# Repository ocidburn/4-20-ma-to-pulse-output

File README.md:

# AM24 — преобразователь 4–20 мА → частота / импульсы

Прототип на NUCLEO-G474RE с изолированным входом на AD7124-4. ТЗ, расчёт погрешностей, описание схемы, перечень элементов с ценами и методика калибровки — в [docs/AM24_spec.pdf](docs/AM24_spec.pdf).

```
docs/       ТЗ и описание схемы (PDF)
firmware/   прошивка STM32G474 (CMake, без HAL, регистры CMSIS)
hardware/   схема и печатная плата шилда (KiCad 10), PDF, перечень элементов, файлы для заказа (fab/)
tools/      утилита на ПК (am24.py), генераторы схемы и печатной платы KiCad (Python)
```

Заголовки CMSIS подключены как подмодули git, поэтому клонируйте с ними:

```bash
git clone --recursive https://github.com/ocidburn/4-20-ma-to-pulse-output.git
```

Если репозиторий уже склонирован без них: `git submodule update --init`. На Windows перед этим может понадобиться `git config --global core.longpaths true`.

## Прошивка

### Сборка

Нужны CMake (есть в `C:\Program Files (x86)\CMake`) и компилятор из STM32CubeIDE 2.1.1 — его путь находится автоматически, другой можно указать через `-DARM_TOOLCHAIN_DIR=<папка bin>`. Ninja тоже берётся из CubeIDE.

```bash
cd firmware
cmake -S . -B build -G Ninja
cmake --build build
```

Результат: `build/am24.elf`, `am24.hex`, `am24.bin` (≈ 35 КБ flash, 10 КБ RAM).
Без TCXO (на внутреннем генераторе, только для отладки): `cmake -S . -B build -G Ninja -DUSE_HSI=ON`.

### Прошивка платы

Проще всего скопировать `build/am24.bin` на диск NOD_G474RE, который Nucleo создаёт при подключении по USB. Либо открыть `am24.elf` в STM32CubeProgrammer.

### Выводы (Arduino-разъём Nucleo)

| Вывод | Arduino | Назначение |
|---|---|---|
| PA5 / PA6 / PA7 | D13 / D12 / D11 | SPI1 SCK / MISO / MOSI → ISO7741 → AD7124 |
| PB6 | D10 | CS AD7124 |
| PA0 | A0 | частотный выход (TIM5_CH1) |
| PA1 | A1 | импульсный выход |
| PA4 | A2 | светодиод «Авария» |
| PA2 / PA3 | — | LPUART1 → виртуальный COM-порт ST-LINK, 115200 8N1 |
| PF0 | — | вход 10 МГц от TCXO (HSE bypass) |
| PB10 | D6 | PPS от модуля GPS (TIM2_CH3), разъём J7 на шилде |

**Перед запуском с TCXO** проверьте по руководству Nucleo-G474RE (UM2505), какие перемычки (solder bridges) перепаять, чтобы подать внешний такт на OSC_IN. Если HSE не запустится, прошивка сама перейдёт на внутренний генератор и сообщит об этом при старте («HSI (inaccurate!)»).

### Как работает

- АЦП: секвенсор перебирает три канала, ≈ 150 мс на круг. Каналы 0 и 1 — шунт в прямом (AIN0−AIN1) и обратном (AIN1−AIN0) порядке: полуразность пары убирает смещение АЦП и его дрейф. Канал 2 — AIN6, делитель термистора NTC от опоры. Биполярный режим, усиление 1, буферы включены (у канала NTC без буфера AIN−), опора REFIN1 = 3,0 В, пост-фильтр 20 отсч./с (подавление 50/60 Гц).
- Температурная поправка: ток × (1 − `tc_ppm`·10⁻⁶·(T − T₀)), где T — температура по NTC, T₀ — запоминается командой `CAL CLEAR`. Затем калибровка — кусочно-линейная, до 11 точек.
- Частота: 32-битный TIM5 на 170 МГц, период в формате 32.32 с дробным накоплением — средняя частота точна до долей ppm, отдельный период отличается не больше чем на 1 такт (5,9 нс).
- Импульсы: каждые 1 мс расход интегрируется от того же генератора; целые импульсы копятся в счётчике и выдаются с заданной длительностью (пауза = длительности). Поправка генератора действует и на импульсы.
- GPS: TIM2 захватывает фронты PPS; ошибка TCXO считается за окно `gps_win` секунд (по умолчанию 100, разрешение ≈ 0,001 ppm) и сразу применяется. Без PPS работает последняя измеренная поправка, после перезапуска — `tcxo_ppm`. На каждом фронте PPS запоминается точная сумма импульсов с дробной частью — по ней утилита проверяет импульсный выход.
- Аварии: ток < `alarm_lo` или > `alarm_hi` (NE43), ошибка АЦП или нет данных 500 мс, переполнение буфера импульсов. Бит 0x10 — термистор не отвечает или температура ушла от калибровочной больше чем на `t_window`: только светодиод, выходы работают.
- Настройки и калибровка хранятся в последней странице flash. **Во время SAVE выходы замирают примерно на 25 мс.**

### Команды (терминал 115200 8N1, каждая строка заканчивается `OK` или `ERR ...`)

| Команда | Что делает |
|---|---|
| `*IDN?` | идентификация |
| `MEAS?` | ток, частота, расход, сумматор, температура, поправка генератора, аварии |
| `RAW?` | ток до калибровки (с поправкой и без), его среднее за 3 с, температура |
| `WIN START` / `WIN?` | окно усреднения: среднее всех пар с момента `WIN START` |
| `CONF?` | все настройки |
| `SET <ключ> <значение>` | изменить настройку (действует сразу, `SAVE` — сохранить) |
| `CAL?` / `CAL CLEAR` / `CAL ADD <мА>` | точки калибровки (до 11); `CAL ADD` берёт среднее окна, если оно открыто |
| `SAVE` / `DEFAULTS` | сохранить / заводские настройки |
| `TOTAL?` / `TOTAL RESET` | сумматор импульсов (`EXACT` — с дробной частью) |
| `GPS?` / `GPS STORE` | состояние PPS и измеренная ошибка генератора / записать её в `tcxo_ppm` (затем `SAVE`) |
| `FTEST <Гц>` / `FTEST OFF` | принудительная частота для калибровки генератора |

Ключи настроек: `fmin`, `fmax` (Гц), `cutoff` (% диапазона), `damp` (с), `qmax` (ед./ч при 20 мА), `pval` (ед./имп), `pwidth` (мс), `ppol` (1 — активный высокий уровень на PA1), `alarm_mode` (0 — 0 Гц, 1 — `alarm_freq`, 2 — удержание), `alarm_freq`, `alarm_lo`, `alarm_hi` (мА), `tcxo_ppm`, `gps` (1 — поправка по GPS), `gps_win` (с), `vref`, `rshunt`, `tc_ppm` (ppm/°C), `t_window` (°C), `ntc_r25`, `ntc_beta`, `ntc_rfix`.

Настройки версии 0.2 несовместимы с 0.1: после прошивки действуют заводские, калибровку нужно выполнить заново.

## Утилита на ПК

```bash
pip install pyserial pyvisa pyvisa-py
python tools/am24.py ports                      # список COM-портов
python tools/am24.py -p COM5 meas --watch       # показания
python tools/am24.py -p COM5 set qmax 50 --save
python tools/am24.py -p COM5 gps                # PPS и ошибка генератора; --store — сохранить её
python tools/am24.py -p COM5 --rref 100.000123 --dmm GPIB0::22::INSTR --dmm-type hp3458 tempco --apply
python tools/am24.py -p COM5 --rref 100.000123 --dmm GPIB0::22::INSTR --dmm-type hp3458 cal
python tools/am24.py -p COM5 --rref 100.000123 --dmm GPIB0::22::INSTR --dmm-type hp3458 verify
python tools/am24.py -p COM5 --rref 100.000123 --dmm GPIB0::22::INSTR --dmm-type hp3458 pulses --seconds 1000
python tools/am24.py -p COM5 log --interval 1   # журнал в CSV
python tools/am24.py --sim cal                  # пробный прогон без железа
```

- `--rref` — сопротивление эталонного резистора из сертификата; `--rref-tc` и `--rref-temp` пересчитывают его на текущую температуру.
- `--dmm` — адрес мультиметра в VISA (GPIB, USB, LAN или COM). `--dmm-type scpi` (по умолчанию) — Keysight, Fluke, Keithley; `hp3458` — язык 3458A. `--dmm-init` задаёт свои команды настройки. Без `--dmm` среднее за окно вводится вручную (запустите статистику на мультиметре, когда утилита попросит).
- `cal` — 9 точек от 4 до 20 мА, выдержка 20 с, окно 60 с (`--points`, `--settle`, `--window`). Утилита усредняет преобразователь (`WIN`) и мультиметр за одно и то же окно и показывает отклонение точек от гладкой кривой — так видна плохая точка.
- `verify` — 10 точек между точками калибровки, допуск `--limit-ppm` (по умолчанию 10 ppm диапазона = 0,001 %), отчёт CSV.
- `tempco` — температурный коэффициент `tc_ppm`: окна по 60 с в течение `--minutes` (по умолчанию 120) при 20 мА, пока температура под крышкой меняется хотя бы на 0,5 °C. Выполнять до калибровки.
- `pulses` — проверка импульсного выхода по времени GPS: дробная сумма импульсов на фронтах PPS против тока эталона за то же число секунд.
- В неопределённость результата `verify` и `pulses` не входит погрешность самого эталона — её считают отдельно (см. документ, раздел «Калибровка и проверка»).

## Плата-шилд (KiCad)

`hardware/am24_shield.kicad_sch` — полная схема на листе A2 (93 элемента), формируется скриптом:

```bash
python tools/gen_wired.py
```

Элементы нарисованы стандартными символами KiCad и соединены проводниками. Шины питания (+24V, +5V, +3V3, +5V_ISO, +3V3_ISO, GND, AGND) показаны символами питания, метки остались только у сигналов FOUT, POUT, ALARM между выходными каскадами и разъёмом Nucleo и у NTC (делитель термистора к AIN6). ERC KiCad 10: 0 ошибок. Рядом лежат `am24_shield.pdf`, нетлист и `am24_shield_bom.csv` — перечень элементов.

Клеммы выходов X3/X4: **1 — OC, 2 — PP (24 В), 3 — 0 В**.

Для режима 0,001 % добавлены термистор RK1 с делителем R9, C33 (ставится вплотную к DA1 и R2, всё под одной крышкой) и разъём J7 для модуля GPS: 1 +5V, 2 +3V3, 3 GND, 4 PPS → R10 → D6.

Старый вариант схемы на метках (`tools/gen_schematic.py`) перезаписывает тот же файл — не запускайте его. Совпадение соединений двух вариантов проверяется так (`am24_shield_labels.net` — нетлист старого варианта):

```bash
cd hardware
python ../tools/cmp_net.py am24_shield_labels.net am24_shield.net
```

- Цоколёвки AD7124-4, ISO7741, LTC6655, ADP7118, NXE1, ASTX-H11 и R-78HB сверены с документацией производителей.
- Стандартные цоколёвки DN2540N5 (G-D-S), NTD3055L104 (G-D-S), BCP56/BCP53 (B-C-E) и BAV199 (1 — анод D1, 2 — катод D2, 3 — общий) из текста документации не подтверждены — сверить с чертежами.
- F1 и F2 (Bourns MF-R005-0 и MF-R050) используют посадочное место `AM24:Fuse_Bourns_MF-R_8.0x3.1mm_P5.10mm` из библиотеки проекта `hardware/am24.pretty` (подключена через `hardware/fp-lib-table`). Сделано по размерам из документации Bourns: шаг 5,1 мм, выводы с двух сторон диска ≈ 1,8 мм друг от друга, отверстия 0,8 мм под выводы 0,405–0,51 мм. Модели SamacSys сюда не кладутся: их лицензия запрещает распространять их в виде библиотеки, а репозиторий публичный. У ADP7118 сверить размер теплового пятна с документацией.
- Добавлены 10 кОм на выводы МК (выходные каскады выключены при сбросе) и балласт R6 270 Ом для NXE1 (модулю нужно не меньше 10 % нагрузки).
- ERC: 0 ошибок, 48 предупреждений. 40 — символы, нарисованные генератором (MOSFET с перенумерованными выводами, прямоугольники микросхем, свои шины питания): они хранятся в самой схеме, отдельной библиотеки `am24` нет. 8 — BC847/BC857: в библиотеке KiCad они заданы через `extends`, а в схеме лежат развёрнутыми.

## Печатная плата

Два варианта одной платы 100 × 90 мм, ставится на разъёмы Arduino поверх NUCLEO-G474RE:

| Файл | Слои | Для чего |
|---|---|---|
| `hardware/am24_shield.kicad_pcb` | 4: сигналы / In1 — сплошные AGND и GND / In2 — сигналы и земля / сигналы и земля | основной: сплошная земля под аналоговой частью |
| `hardware/am24_shield_2layer.kicad_pcb` | 2: сигналы и заливка землёй с двух сторон | дешевле |

Файлы для заказа (Gerber, сверловка, координаты элементов) — `hardware/fab/*_fab.zip`, загружаются на JLCPCB или PCBWay как есть. Правила под их возможности: дорожка от 0,15 мм (обычно 0,2–0,3), зазор 0,2 мм, переходное 0,6/0,3 мм.

Как устроена плата:

- **Совмещение с Nucleo.** Разъёмы XS1–XS4 стоят в точках Arduino Uno R3 и ставятся снизу платы, штырями вниз в гнёзда Nucleo. Положение гнёзд и разъёмов Morpho на Nucleo-64 взято из стандарта Arduino и открытых посадочных мест Nucleo-64; **перед заказом распечатайте плату 1:1 и приложите к Nucleo**.
- **Выводные элементы только за пределами Nucleo.** Над Nucleo — только SMD, чтобы выводы не упирались в её детали и в штыри Morpho. Клеммники, TO-220, R-78, предохранители и J7 стоят на выступающей части платы.
- **Перемычки к Morpho.** CN7 оказывается под платой, поэтому над его выводами 29 (PF0, такт TCXO) и 6 (E5V, питание 5 В) прорезаны окна. J6 и J5 — SMD-штыри рядом с окнами; провод с гнёздами проходит через окно к выводу Morpho.
- **Изоляция.** Изолированная часть (вход, шунт, АЦП, ИОН, изолированное питание) — левый нижний угол. Барьер — полоса 4 мм без меди на всех слоях; через него переходят только ISO7741 (DD2) и NXE1 (U1). Земли: AGND на изолированной стороне, GND на остальной.
- **Шунт.** Измерительные линии S+ и S− проложены вручную прямо от площадок R2 к R3 и R4. Ток петли входит в R2.1 и выходит из R2.2 отдельными дорожками.
- **Крышка и радиатор.** Аналоговое ядро обведено на шелкографии («COVER») — сюда ставится крышка. Слева от VT1 место под небольшой радиатор TO-220 (на слое Fab).
- **OC-выходы.** Под DPAK VT21/VT22 — медные полигоны стока на трёх слоях (на 4-слойной) со сквозными переходными: тепло при КЗ на выходе.

Плата формируется скриптами (KiCad 10, Python KiCad и [Freerouting](https://github.com/freerouting/freerouting) 2.5, нужна Java 21+):

```bash
"C:\Program Files\KiCad\10.0\bin\python.exe" tools/gen_pcb.py --layers 4      # расстановка, барьер, правила, ручные дорожки
"C:\Program Files\KiCad\10.0\bin\python.exe" tools/route_pcb.py hardware/am24_shield.kicad_pcb --jar freerouting-2.5.0.jar
python tools/export_fab.py                                                      # архивы для заказа
```

`gen_pcb.py` перезаписывает плату: ручные правки в KiCad при этом теряются. Автотрассировщик каждый раз раскладывает дорожки немного по-разному.

DRC KiCad 10 для обоих вариантов: нет неразведённых цепей, нарушений зазоров и замыканий. Остаются предупреждения шелкографии (надписи частично налезают друг на друга и на площадки — завод срезает шелкографию с площадок сам) и одно о тепловом соединении площадки с заливкой. Превью: `hardware/am24_shield_top.png`, `am24_shield_bottom.png`, `am24_shield_2layer_top.png`; сборочный чертёж верхней стороны — `am24_shield_assembly_top.pdf`.

## Что не проверено

- Прошивка собрана, но на реальной плате не запускалась: нет железа. Обработка пар, температурная поправка, окна и GPS проверены только на симуляторе утилиты (`--sim`), он повторяет протокол, но не код прошивки.
- Команды мультиметров в `am24.py` (SCPI и язык 3458A) на приборах не проверялись.
- Адреса регистров AD7124, битовые поля и коды (пост-фильтр 20 отсч./с = FILTER 7 / POST_FILTER 5, режим full power = 2, ID 0x04/0x06/0x07) сверены с официальным драйвером ADI [no-OS ad7124.h / ad7124.c](https://github.com/analogdevicesinc/no-OS/tree/main/drivers/adc/ad7124). Электрические пределы (диапазон входов с буферами AVSS + 0,1 … AVDD − 0,1 В, опора 3,0 В при AVDD 3,3 В) сверены с документацией AD7124-4, ред. E.
- CRC на SPI АЦП не включён; связь контролируется флагом ошибки и тайм-аутом данных.
- Время установления АЦП при переключении трёх каналов взято равным периоду пост-фильтра (50 мс); на плате проверить по флагам и частоте пар.
- Плата не изготавливалась. Положение разъёмов Nucleo-64 и Morpho взято из стандарта Arduino и открытых посадочных мест, а не из чертежа ST: перед заказом сверить распечаткой 1:1.
- Медь стока под DPAK VT21/VT22 — около 0,7 см² на слой (≈ 2,2 см² на 4-слойной, ≈ 1,5 см² на 2-слойной), меньше 6 см² из расчёта. При длительном КЗ выхода OC на 30 В транзистор сильно греется; если такой режим возможен, снизить порог ограничения тока или увеличить полигон.
- Радиатор VT1 не выбран: на плате только место под него.

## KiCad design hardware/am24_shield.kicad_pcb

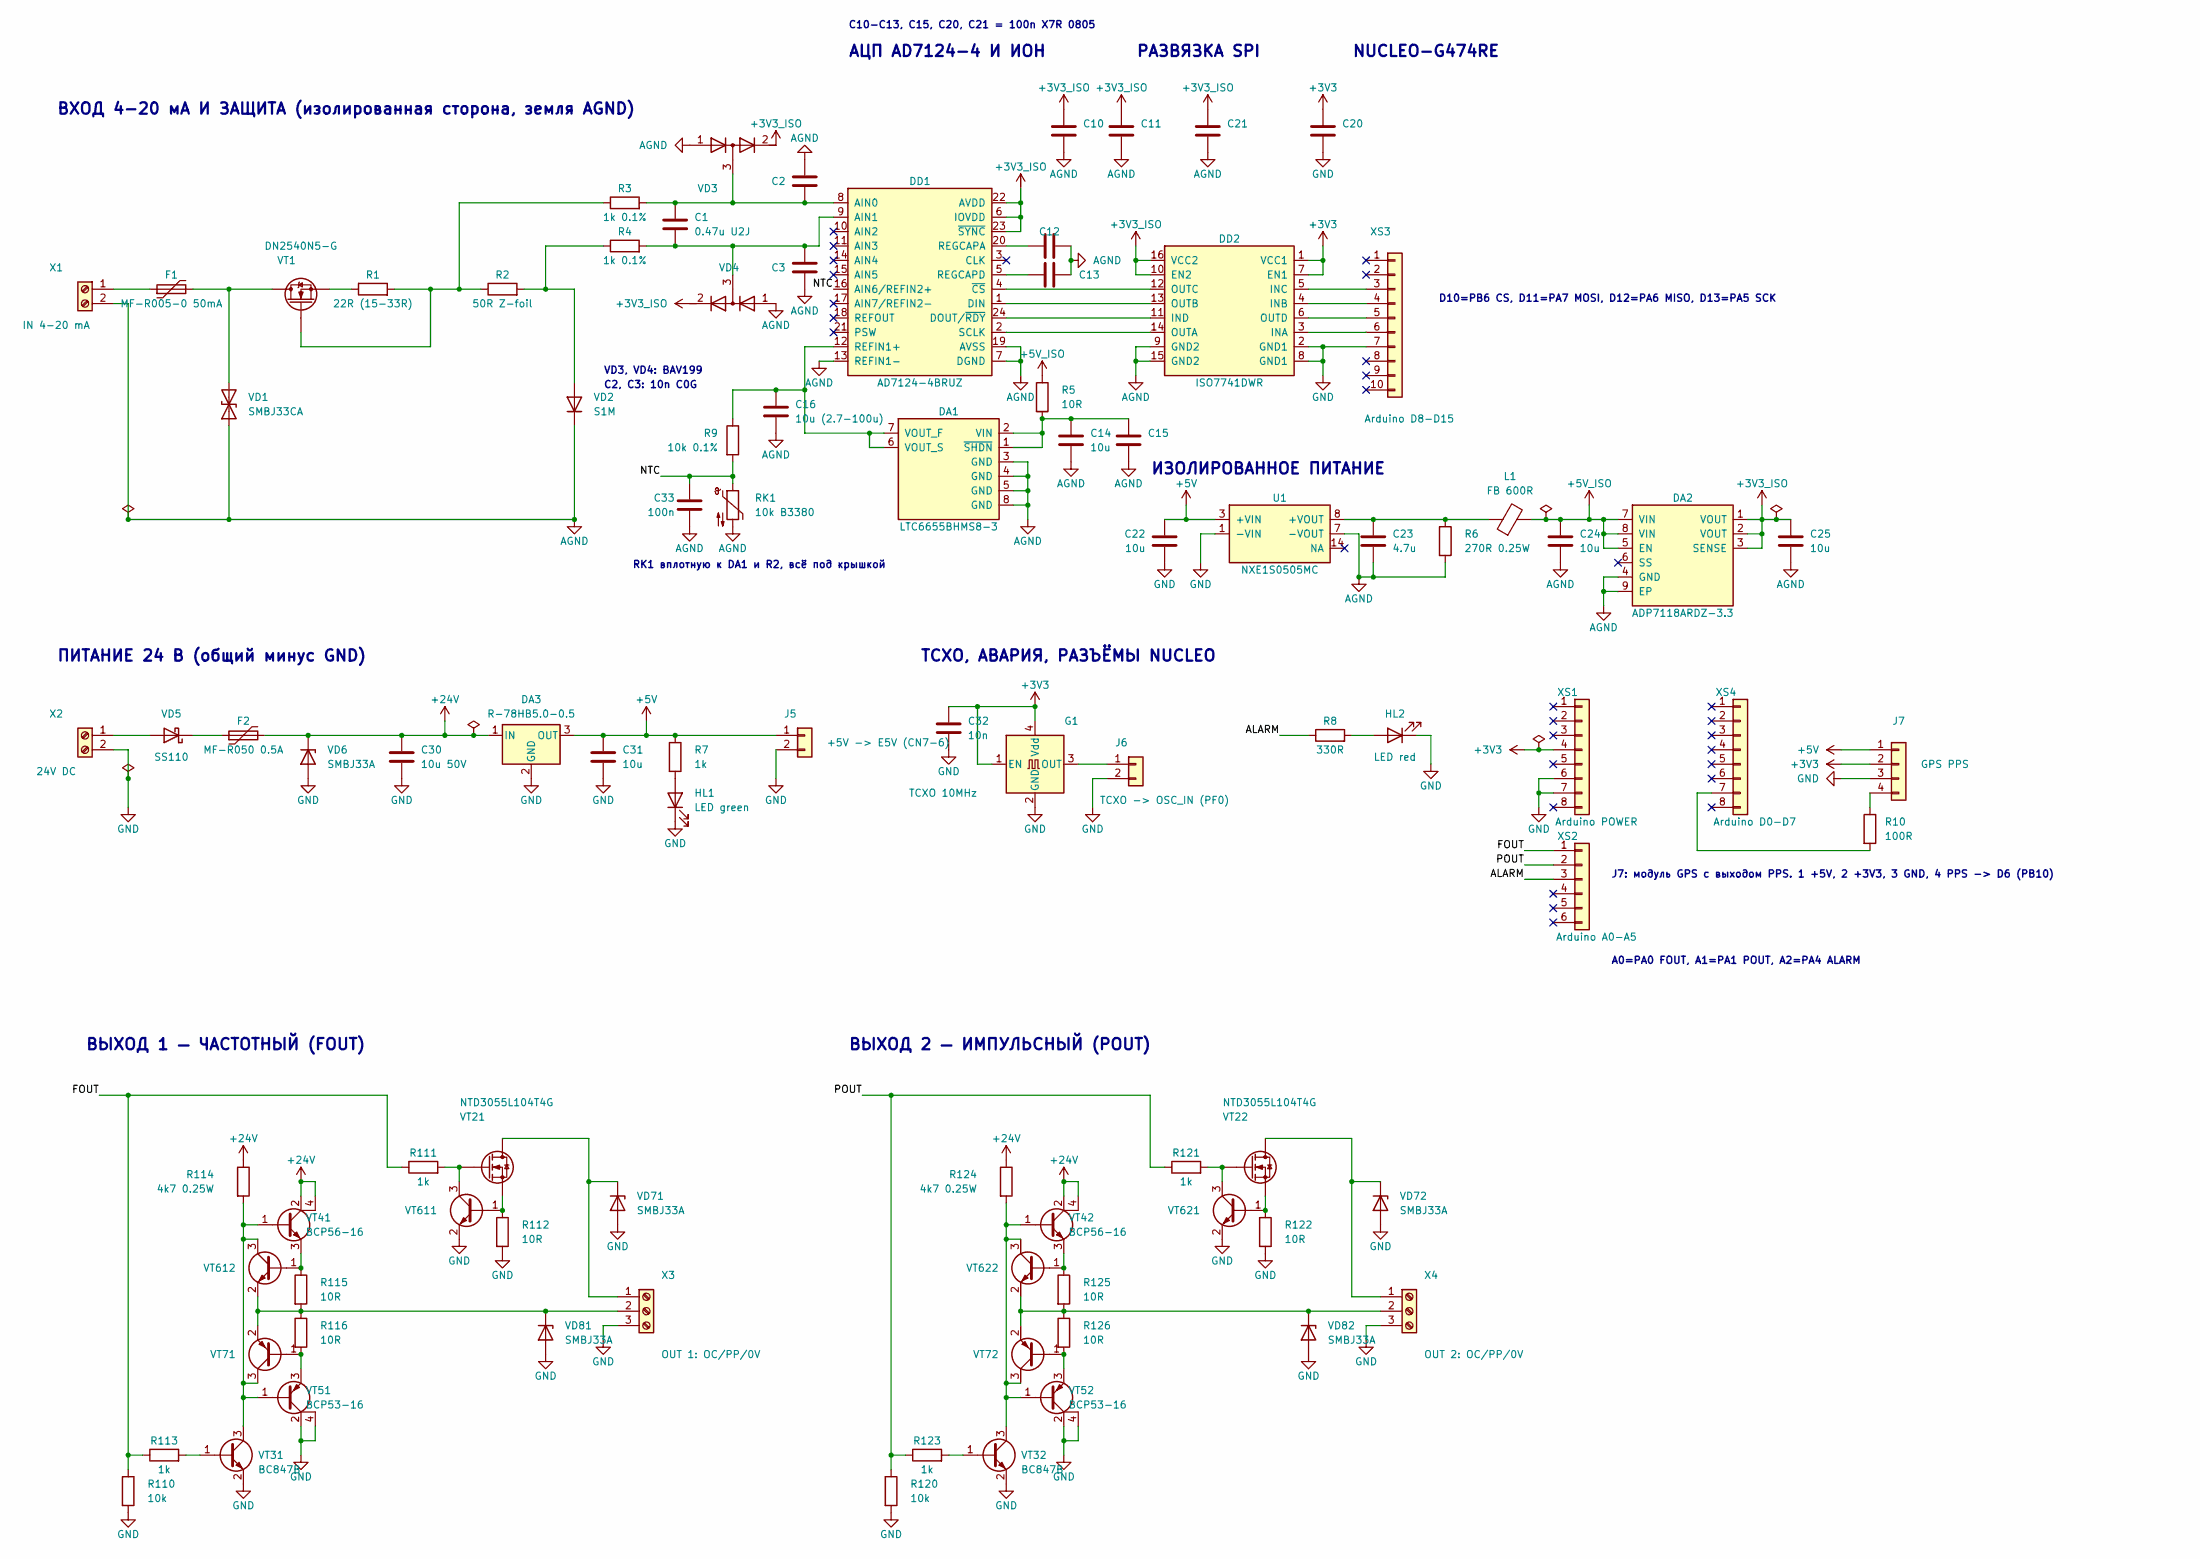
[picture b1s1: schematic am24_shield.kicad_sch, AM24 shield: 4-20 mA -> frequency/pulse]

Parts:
C1: 0.47u U2J; C_1812_4532Metric; MPN C1812C474J5JACTU
C2, C3: 10n C0G; C_0805_2012Metric
C10, C11, C12, C13, C15, C20, C21, C33: 100n; C_0805_2012Metric
C14, C22, C24, C25, C31: 10u; C_1206_3216Metric
C16: 10u (2.7-100u); C_1206_3216Metric
C23: 4.7u; C_1206_3216Metric
C30: 10u 50V; C_1210_3225Metric
C32: 10n; C_0805_2012Metric
DA1: LTC6655BHMS8-3; MSOP-8_3x3mm_P0.65mm; MPN LTC6655BHMS8-3#PBF
DA2: ADP7118ARDZ-3.3; SOIC-8-1EP_3.9x4.9mm_P1.27mm_EP2.29x3mm; MPN ADP7118ARDZ-3.3
DA3: R-78HB5.0-0.5; Converter_DCDC_RECOM_R-78HB-0.5_THT; MPN R-78HB5.0-0.5
DD1: AD7124-4BRUZ; TSSOP-24_4.4x7.8mm_P0.65mm; MPN AD7124-4BRUZ
DD2: ISO7741DWR; SOIC-16W_7.5x10.3mm_P1.27mm; MPN ISO7741DWR
F1: MF-R005-0 50mA; Fuse_Bourns_MF-R_8.0x3.1mm_P5.10mm; MPN MF-R005-0
F2: MF-R050 0.5A; Fuse_Bourns_MF-R_8.0x3.1mm_P5.10mm; MPN MF-R050
G1: TCXO 10MHz; Oscillator_SMD_Abracon_ASE-4Pin_3.2x2.5mm; MPN ASTX-H11-10.000MHZ-T
HL1: LED green; LED_0805_2012Metric
HL2: LED red; LED_0805_2012Metric
J5: +5V -> E5V (CN7-6); PinHeader_1x02_P2.54mm_Vertical_SMD_Pin1Left
J6: TCXO -> OSC_IN (PF0); PinHeader_1x02_P2.54mm_Vertical_SMD_Pin1Left
J7: GPS PPS; PinHeader_1x04_P2.54mm_Vertical
L1: FB 600R; L_0603_1608Metric; MPN BLM18KG601SN1D
R1: 22R (15-33R); R_0805_2012Metric
R2: 50R Z-foil; R_0805_2012Metric; MPN Y402250R0000A9R
R3, R4: 1k 0.1%; R_0805_2012Metric; MPN ERA-6AEB102V
R5, R112, R115, R116, R122, R125, R126: 10R; R_0805_2012Metric
R6: 270R 0.25W; R_1206_3216Metric
R7, R111, R113, R121, R123: 1k; R_0805_2012Metric
R8: 330R; R_0805_2012Metric
R9: 10k 0.1%; R_0805_2012Metric; MPN ERA-6AEB103V
R10: 100R; R_0805_2012Metric
R110, R120: 10k; R_0805_2012Metric
R114, R124: 4k7 0.25W; R_1206_3216Metric
RK1: 10k B3380; R_0603_1608Metric; MPN NCU18XH103F60RB
U1: NXE1S0505MC; Converter_DCDC_Murata_NXExSxxxxMC_SMD; MPN NXE1S0505MC-R7
VD1: SMBJ33CA; D_SMB; MPN SMBJ33CA-13-F
VD2: S1M; D_SMA; MPN S1M
VD3, VD4: BAV199; SOT-23; MPN BAV199,215
VD5: SS110; D_SMA; MPN SS110
VD6, VD71, VD72, VD81, VD82: SMBJ33A; D_SMB; MPN SMBJ33ATR
VT1: DN2540N5-G; TO-220-3_Vertical; MPN DN2540N5-G
VT21, VT22: NTD3055L104T4G; TO-252-2; MPN NTD3055L104T4G
VT31, VT32, VT611, VT612, VT621, VT622: BC847B; SOT-23; MPN BC847B,215
VT41, VT42: BCP56-16; SOT-223-3_TabPin2; MPN BCP56-16T1G
VT51, VT52: BCP53-16; SOT-223-3_TabPin2; MPN BCP5316QTA
VT71, VT72: BC857B; SOT-23; MPN BC857B,215
X1: IN 4-20 mA; TerminalBlock_Phoenix_MKDS-1,5-2-5.08_1x02_P5.08mm_Horizont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
X2: 24V DC; TerminalBlock_Phoenix_MKDS-1,5-2-5.08_1x02_P5.08mm_Horizont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
X3: OUT 1: OC/PP/0V; TerminalBlock_Phoenix_MKDS-1,5-3-5.08_1x03_P5.08mm_Horizont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
X4: OUT 2: OC/PP/0V; TerminalBlock_Phoenix_MKDS-1,5-3-5.08_1x03_P5.08mm_Horizont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
XS1: Arduino POWER; PinHeader_1x08_P2.54mm_Vertical
XS2: Arduino A0-A5; PinHeader_1x06_P2.54mm_Vertical
XS3: Arduino D8-D15; PinHeader_1x10_P2.54mm_Vertical
XS4: Arduino D0-D7; PinHeader_1x08_P2.54mm_Vertical

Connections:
+3V3: C20.1, C32.1, DD2.1 (VCC1), DD2.7 (EN1), G1.1 (EN), G1.4 (Vdd), J7.2, XS1.4
+3V3_ISO: C10.1, C11.1, C21.1, C25.1, DA2.1 (VOUT), DA2.2 (VOUT), DA2.3 (SENSE), DD1.6 (IOVDD), DD1.22 (AVDD), DD1.23 (~SYNC), DD2.10 (EN2), DD2.16 (VCC2), VD3.2 (K), VD4.2 (K)
+5V: C22.1, C31.1, DA3.3 (OUT), J5.1, J7.1, R7.1, U1.3 (+VIN)
+5V_ISO: C24.1, DA2.5 (EN), DA2.7 (VIN), DA2.8 (VIN), L1.2, R5.1
+24V: C30.1, DA3.1 (IN), F2.2, R114.1, R124.1, VD6.1 (K), VT41.2 (C), VT41.4 (C), VT42.2 (C), VT42.4 (C)
/ALARM: R8.1, XS2.3
/FOUT: R110.1, R111.1, R113.1, XS2.1
/NTC: C33.1, DD1.16 (AIN6/REFIN2+), R9.2, RK1.1
/POUT: R120.1, R121.1, R123.1, XS2.2
AGND: C2.1, C3.2, C10.2, C11.2, C12.2, C13.2, C14.2, C15.2, C16.2, C21.2, C23.2, C24.2, C25.2, C33.2, DA1.3 (GND), DA1.4 (GND), DA1.5 (GND), DA1.8 (GND), DA2.4 (GND), DA2.9 (EP), DD1.7 (DGND), DD1.13 (REFIN1-), DD1.19 (AVSS), DD2.9 (GND2), DD2.15 (GND2), R6.2, RK1.2, U1.7 (-VOUT), VD1.1 (A1), VD2.1 (K), VD3.1 (A), VD4.1 (A), X1.2
GND: C20.2, C22.2, C30.2, C31.2, C32.2, DA3.2 (GND), DD2.2 (GND1), DD2.8 (GND1), G1.2 (GND), HL1.1 (K), HL2.1 (K), J5.2, J6.2, J7.3, R110.2, R112.2, R120.2, R122.2, U1.1 (-VIN), VD6.2 (A), VD71.2 (A), VD72.2 (A), VD81.2 (A), VD82.2 (A), VT31.2 (E), VT32.2 (E), VT51.2 (C), VT51.4 (C), VT52.2 (C), VT52.4 (C), VT611.2 (E), VT621.2 (E), X2.2, X3.3, X4.3, XS1.6, XS1.7, XS3.7
unnamed: C14.1, C15.1, DA1.1 (~SHDN), DA1.2 (VIN), R5.2
unnamed: C16.1, DA1.6 (VOUT_S), DA1.7 (VOUT_F), DD1.12 (REFIN1+), R9.1
unnamed: C1.1, C2.2, DD1.8 (AIN0), R3.2, VD3.3 (common)
unnamed: C1.2, C3.1, DD1.9 (AIN1), R4.2, VD4.3 (common)
unnamed: DD1.1 (DIN), DD2.13 (OUTB)
unnamed: DD1.24 (DOUT/~RDY), DD2.11 (IND)
unnamed: C12.1, DD1.20 (REGCAPA)
unnamed: C13.1, DD1.5 (REGCAPD)
unnamed: DD1.2 (SCLK), DD2.14 (OUTA)
unnamed: DD1.4 (~CS), DD2.12 (OUTC)
unnamed: DD2.3 (INA), XS3.6
unnamed: DD2.4 (INB), XS3.4
unnamed: DD2.5 (INC), XS3.3
unnamed: DD2.6 (OUTD), XS3.5
unnamed: G1.3 (OUT), J6.1
unnamed: HL1.2 (A), R7.2
unnamed: HL2.2 (A), R8.2
unnamed: J7.4, R10.1
unnamed: C23.1, L1.1, R6.1, U1.8 (+VOUT)
unnamed: F1.2, VD1.2 (A2), VT1.2 (D)
unnamed: R2.2, R4.1, VD2.2 (A)
unnamed: VD5.2 (A), X2.1
unnamed: F2.1, VD5.1 (K)
unnamed: VD71.1 (K), VT21.2 (D), X3.1
unnamed: VD72.1 (K), VT22.2 (D), X4.1
unnamed: R115.2, R116.1, VD81.1 (K), VT71.2 (E), VT612.2 (E), X3.2
unnamed: R125.2, R126.1, VD82.1 (K), VT72.2 (E), VT622.2 (E), X4.2
unnamed: R1.2, R2.1, R3.1, VT1.1 (G)
unnamed: R1.1, VT1.3 (S)
unnamed: R111.2, VT21.1 (G), VT611.3 (C)
unnamed: R112.1, VT21.3 (S), VT611.1 (B)
unnamed: R121.2, VT22.1 (G), VT621.3 (C)
unnamed: R122.1, VT22.3 (S), VT621.1 (B)
unnamed: R113.2, VT31.1 (B)
unnamed: R114.2, VT31.3 (C), VT41.1 (B), VT51.1 (B), VT71.3 (C), VT612.3 (C)
unnamed: R123.2, VT32.1 (B)
unnamed: R124.2, VT32.3 (C), VT42.1 (B), VT52.1 (B), VT72.3 (C), VT622.3 (C)
unnamed: R115.1, VT41.3 (E), VT612.1 (B)
unnamed: R125.1, VT42.3 (E), VT622.1 (B)
unnamed: R116.2, VT51.3 (E), VT71.1 (B)
unnamed: R126.2, VT52.3 (E), VT72.1 (B)
unnamed: F1.1, X1.1
unnamed: R10.2, XS4.7

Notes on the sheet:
ВХОД 4-20 мА И ЗАЩИТА (изолированная сторона, земля AGND)
VD3, VD4: BAV199
C2, C3: 10n C0G
АЦП AD7124-4 И ИОН
RK1 вплотную к DA1 и R2, всё под крышкой
РАЗВЯЗКА SPI
NUCLEO-G474RE
D10=PB6 CS, D11=PA7 MOSI, D12=PA6 MISO, D13=PA5 SCK
C10-C13, C15, C20, C21 = 100n X7R 0805
ИЗОЛИРОВАННОЕ ПИТАНИЕ
ПИТАНИЕ 24 В (общий минус GND)
TCXO, АВАРИЯ, РАЗЪЁМЫ NUCLEO
A0=PA0 FOUT, A1=PA1 POUT, A2=PA4 ALARM
J7: модуль GPS с выходом PPS. 1 +5V, 2 +3V3, 3 GND, 4 PPS -> D6 (PB10)
ВЫХОД 1 — ЧАСТОТНЫЙ (FOUT)
ВЫХОД 2 — ИМПУЛЬСНЫЙ (POUT)

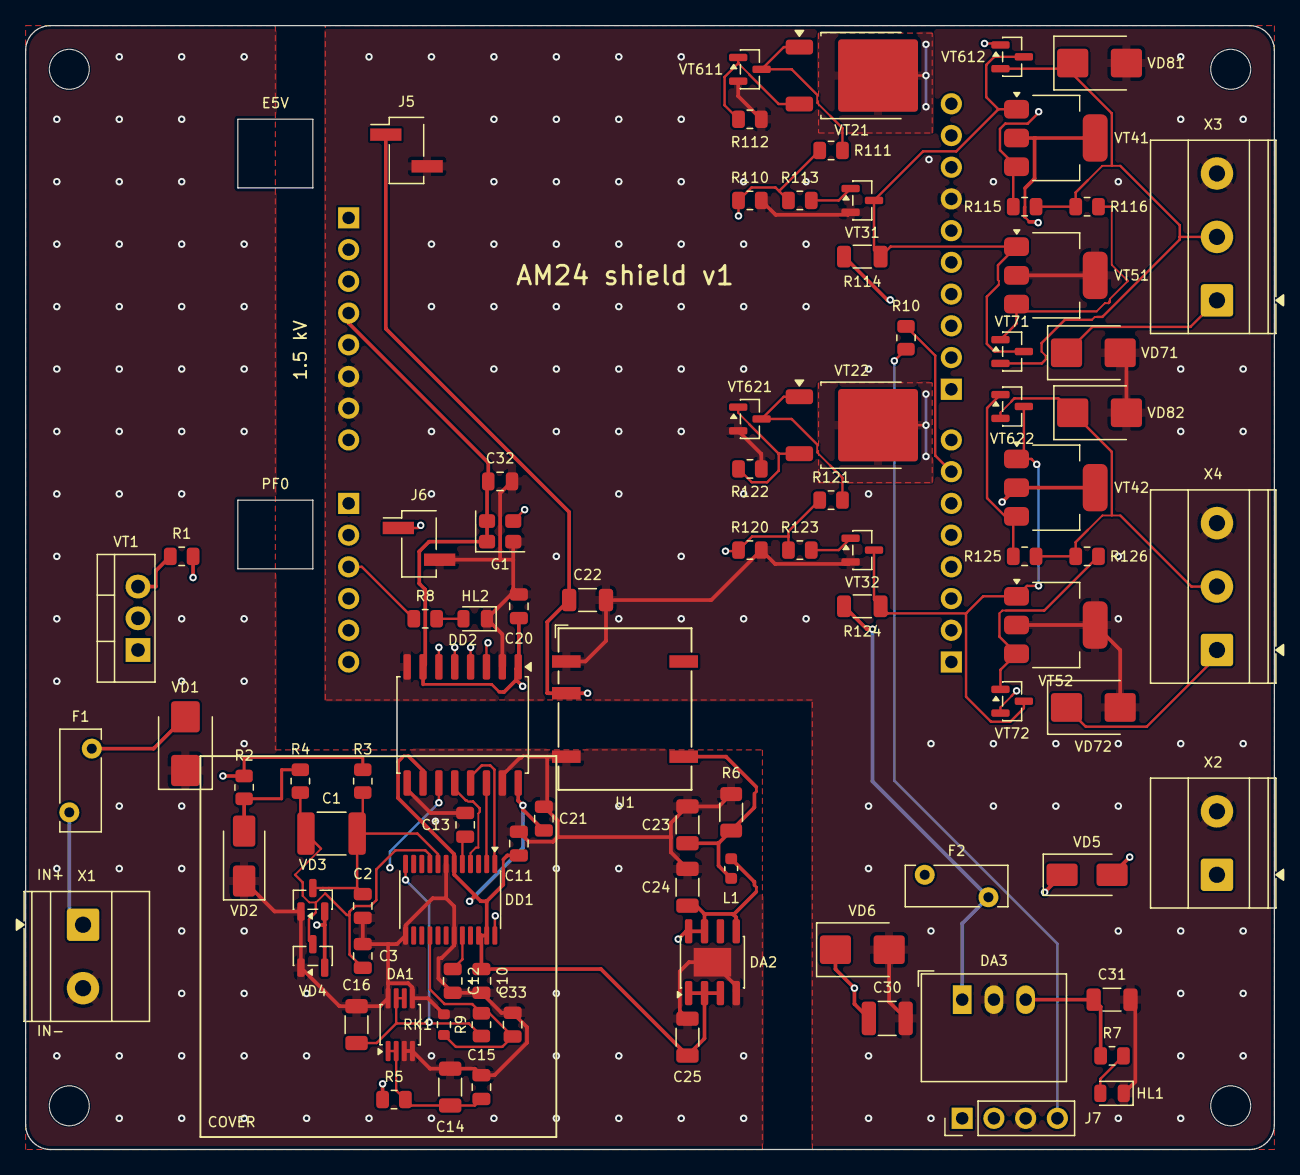
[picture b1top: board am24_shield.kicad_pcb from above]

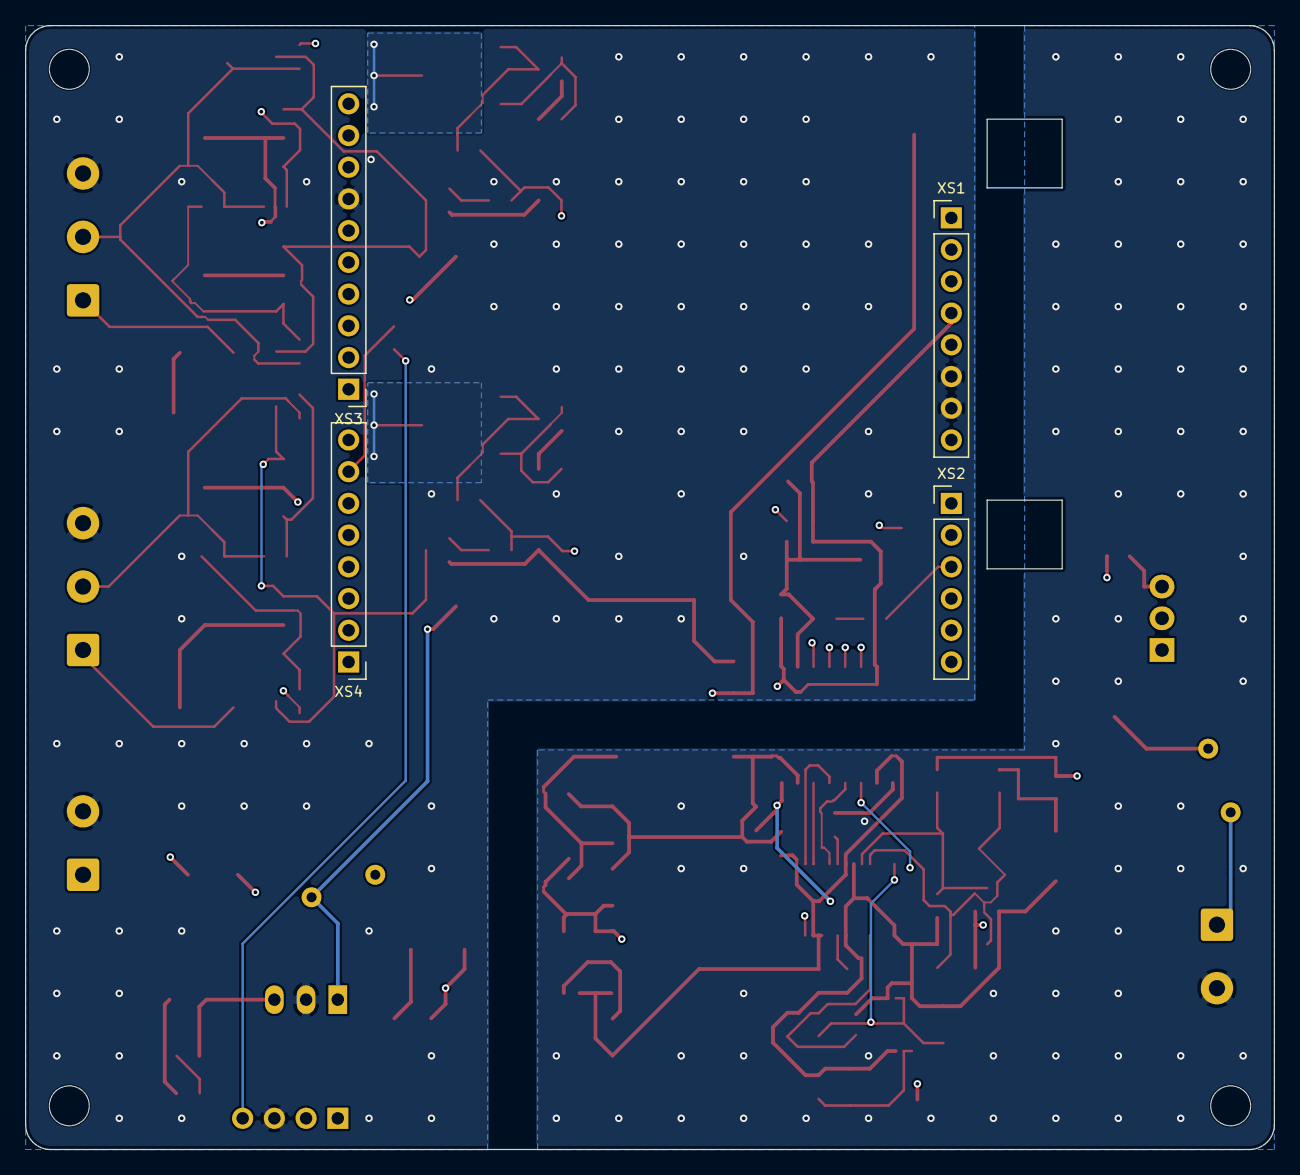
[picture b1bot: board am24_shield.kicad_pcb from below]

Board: 4 copper layers, 100.0 x 90.0 mm, 97 parts (4 on the bottom side), 54 nets.

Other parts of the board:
H1, H2, H3, H4: MountingHole_3.2mm_M3

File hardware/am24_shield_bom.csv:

refs;qty;value;mpn;footprint
C1;1;0.47u 50V U2J;C1812C474J5JACTU;Capacitor_SMD:C_1812_4532Metric
C2 C3;2;10n C0G;;Capacitor_SMD:C_0805_2012Metric
C10 C11 C12 C13 C15 C20 C21 C33;8;100n;;Capacitor_SMD:C_0805_2012Metric
C14 C22 C24 C25 C31;5;10u 16V;;Capacitor_SMD:C_1206_3216Metric
C16;1;10u 16V (2.7-100u req.);;Capacitor_SMD:C_1206_3216Metric
C23;1;4.7u 16V;;Capacitor_SMD:C_1206_3216Metric
C30;1;10u 50V;;Capacitor_SMD:C_1210_3225Metric
C32;1;10n;;Capacitor_SMD:C_0805_2012Metric
DA1;1;LTC6655BHMS8-3;LTC6655BHMS8-3#PBF;Package_SO:MSOP-8_3x3mm_P0.65mm
DA2;1;ADP7118ARDZ-3.3;ADP7118ARDZ-3.3;Package_SO:SOIC-8-1EP_3.9x4.9mm_P1.27mm_EP2.29x3mm
DA3;1;R-78HB5.0-0.5;R-78HB5.0-0.5;Converter_DCDC:Converter_DCDC_RECOM_R-78HB-0.5_THT
DD1;1;AD7124-4BRUZ;AD7124-4BRUZ;Package_SO:TSSOP-24_4.4x7.8mm_P0.65mm
DD2;1;ISO7741DWR;ISO7741DWR;Package_SO:SOIC-16W_7.5x10.3mm_P1.27mm
F1;1;MF-R005-0 50mA;MF-R005-0;AM24:Fuse_Bourns_MF-R_8.0x3.1mm_P5.10mm
F2;1;MF-R050 0.5A;MF-R050;AM24:Fuse_Bourns_MF-R_8.0x3.1mm_P5.10mm
G1;1;ASTX-H11-10.000MHZ-T;ASTX-H11-10.000MHZ-T;Oscillator:Oscillator_SMD_Abracon_ASE-4Pin_3.2x2.5mm
HL1;1;LED green;;LED_SMD:LED_0805_2012Metric
HL2;1;LED red;;LED_SMD:LED_0805_2012Metric
J5;1;+5V -> E5V (CN7-6);;Connector_PinHeader_2.54mm:PinHeader_1x02_P2.54mm_Vertical_SMD_Pin1Left
J6;1;TCXO -> OSC_IN (PF0);;Connector_PinHeader_2.54mm:PinHeader_1x02_P2.54mm_Vertical_SMD_Pin1Left
J7;1;GPS PPS: +5V, +3V3, GND, PPS;;Connector_PinHeader_2.54mm:PinHeader_1x04_P2.54mm_Vertical
L1;1;BLM18KG601SN1D;BLM18KG601SN1D;Inductor_SMD:L_0603_1608Metric
R1;1;22R (select 15-33R);;Resistor_SMD:R_0805_2012Metric
R2;1;50R Z-foil 0.05%;Y402250R0000A9R;Resistor_SMD:R_0805_2012Metric
R3 R4;2;1k 0.1% 25ppm;ERA-6AEB102V;Resistor_SMD:R_0805_2012Metric
R6;1;270R 0.25W ballast;;Resistor_SMD:R_1206_3216Metric
R8;1;330R;;Resistor_SMD:R_0805_2012Metric
R9;1;10k 0.1% 25ppm;ERA-6AEB103V;Resistor_SMD:R_0805_2012Metric
R10;1;100R;;Resistor_SMD:R_0805_2012Metric
R110 R120;2;10k;;Resistor_SMD:R_0805_2012Metric
R111 R113 R121 R123 R7;5;1k;;Resistor_SMD:R_0805_2012Metric
R112 R115 R116 R122 R125 R126 R5;7;10R;;Resistor_SMD:R_0805_2012Metric
R114 R124;2;4k7 0.25W;;Resistor_SMD:R_1206_3216Metric
RK1;1;NTC 10k 1% B25/50 3380K;NCU18XH103F60RB;Resistor_SMD:R_0603_1608Metric
U1;1;NXE1S0505MC-R7;NXE1S0505MC-R7;Converter_DCDC:Converter_DCDC_Murata_NXExSxxxxMC_SMD
VD1;1;SMBJ33CA;SMBJ33CA-13-F;Diode_SMD:D_SMB
VD2;1;S1M;S1M;Diode_SMD:D_SMA
VD3 VD4;2;BAV199;BAV199,215;Package_TO_SOT_SMD:SOT-23
VD5;1;SS110;SS110;Diode_SMD:D_SMA
VD6 VD71 VD72 VD81 VD82;5;SMBJ33A;SMBJ33ATR;Diode_SMD:D_SMB
VT1;1;DN2540N5-G;DN2540N5-G;Package_TO_SOT_THT:TO-220-3_Vertical
VT21 VT22;2;NTD3055L104T4G;NTD3055L104T4G;Package_TO_SOT_SMD:TO-252-2
VT31 VT32 VT611 VT612 VT621 VT622;6;BC847B;BC847B,215;Package_TO_SOT_SMD:SOT-23
VT41 VT42;2;BCP56-16;BCP56-16T1G;Package_TO_SOT_SMD:SOT-223-3_TabPin2
VT51 VT52;2;BCP53-16;BCP5316QTA;Package_TO_SOT_SMD:SOT-223-3_TabPin2
VT71 VT72;2;BC857B;BC857B,215;Package_TO_SOT_SMD:SOT-23
X1;1;IN 4-20 mA;;TerminalBlock_Phoenix:TerminalBlock_Phoenix_MKDS-1,5-2-5.08_1x02_P5.08mm_Horizontal
X2;1;24V DC;;TerminalBlock_Phoenix:TerminalBlock_Phoenix_MKDS-1,5-2-5.08_1x02_P5.08mm_Horizontal
X3;1;OUT1 PP/OC/0V;;TerminalBlock_Phoenix:TerminalBlock_Phoenix_MKDS-1,5-3-5.08_1x03_P5.08mm_Horizontal
X4;1;OUT2 PP/OC/0V;;TerminalBlock_Phoenix:TerminalBlock_Phoenix_MKDS-1,5-3-5.08_1x03_P5.08mm_Horizontal
XS1;1;Arduino POWER;;Connector_PinHeader_2.54mm:PinHeader_1x08_P2.54mm_Vertical
XS2;1;Arduino A0-A5;;Connector_PinHeader_2.54mm:PinHeader_1x06_P2.54mm_Vertical
XS3;1;Arduino D8-D15;;Connector_PinHeader_2.54mm:PinHeader_1x10_P2.54mm_Vertical
XS4;1;Arduino D0-D7;;Connector_PinHeader_2.54mm:PinHeader_1x08_P2.54mm_Vertical

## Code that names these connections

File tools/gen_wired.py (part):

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    for p in ("10", "11", "14", "15", "17", "18", "21", "3"):
        s.nc(f"DD1.{p}")
    x, y = s.P("DD1.16")
    s.label("NTC", (x - s.dx, y), 180)                      # AIN6: NTC divider below
    s.w("DD1.13", (142.24, 73.66))
    s.pwr("AGND", 142.24, 73.66)
    s.w("DD1.22", (177.8, 45.72))
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    s.w("R9.2", "RK1.1")
    s.w((127.0, 93.98), (119.38, 93.98), "C33.1")
    s.w((119.38, 93.98), (114.3, 93.98))
    s.label("NTC", (114.3, 93.98), 180)
    s.pwr("AGND", *s.P("RK1.2"), raw=True)
    s.pwr("AGND", *s.P("C33.2"), raw=True)
    s.text("RK1 вплотную к DA1 и R2, всё под крышкой", 109.22, 110.49, 1.27)
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    two(s, "R8", R, "330R", R0805, 219.71, 139.7, H)
    s.add("HL2", LED, "LED red", "LED_SMD:LED_0805_2012Metric", 231.14, 139.7, 180, ref_at=(231.14, 135.89, None), val_at=(231.14, 143.51, None))
    s.w((210.82, 139.7), "R8.1")
    s.label("ALARM", (210.82, 139.7), 180)
    s.w("R8.2", "HL2.2")
    s.w("HL2.1", (237.49, 139.7), (237.49, 144.78))
    s.pwr("GND", 237.49, 144.78)
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        s.label(net, (x - 5.08 - s.dx, y), 180)
    for p in ("4", "5", "6"):
        s.nc(f"XS2.{p}")
    s.text("A0=PA0 FOUT, A1=PA1 POUT, A2=PA4 ALARM", 269.24, 180.34, 1.27)
    s.add("XS4", CONN[8], "Arduino D0-D7", PH.format(8), 292.1, 142.24, 0, ref_at=(289.56, 132.08, None), val_at=(294.64, 154.94, None))
    for p in range(1, 9):
        if p != 7:
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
